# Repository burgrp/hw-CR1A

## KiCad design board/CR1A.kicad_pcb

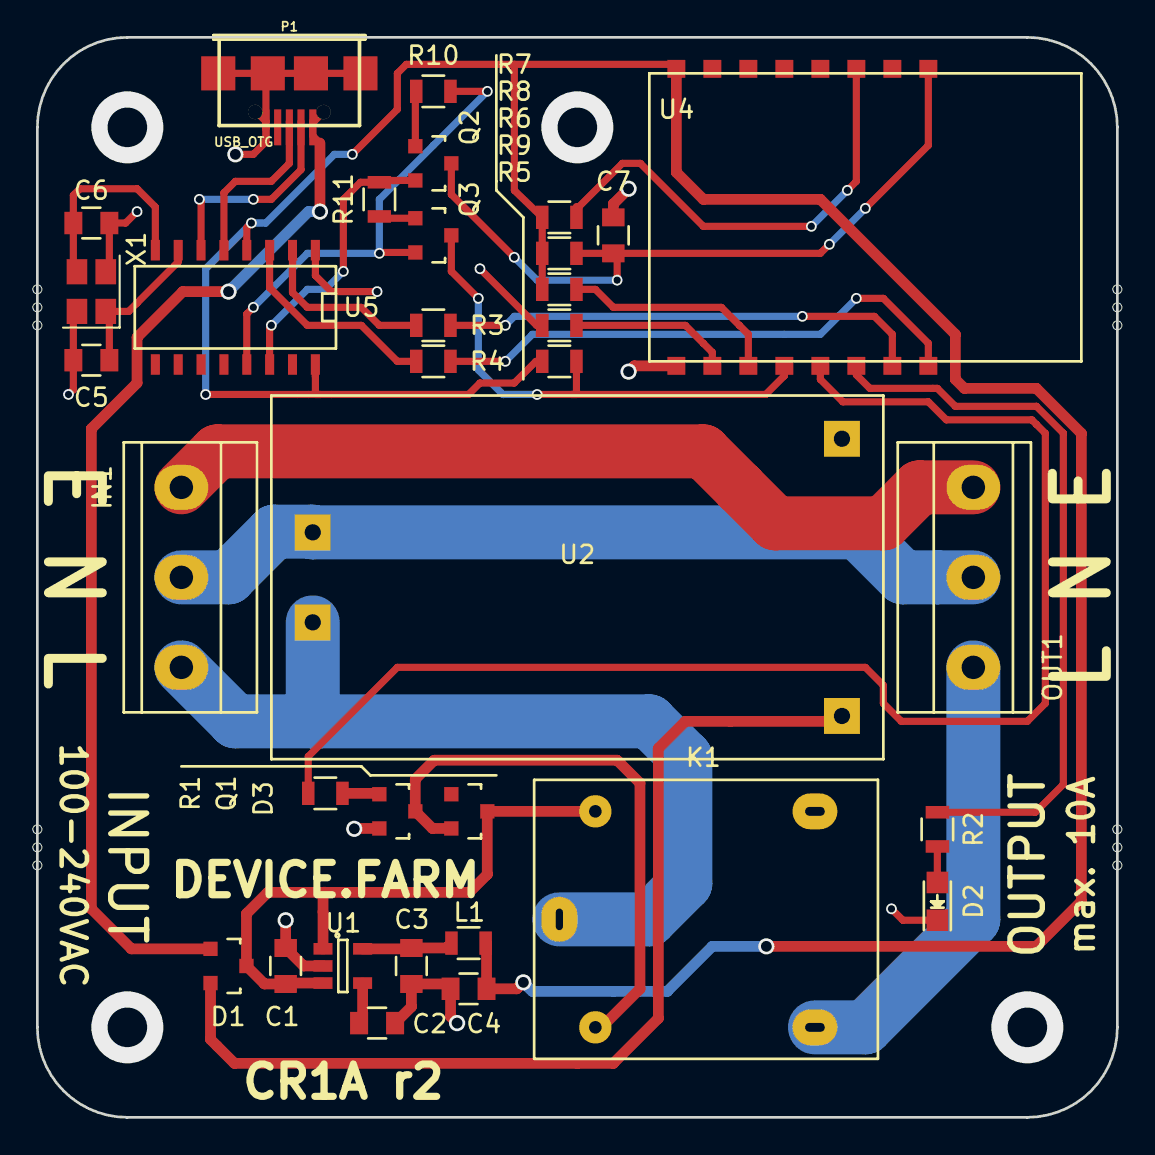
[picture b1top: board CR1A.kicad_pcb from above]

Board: 2 copper layers, 60.0 x 60.0 mm, 38 parts (0 on the bottom side), 33 nets.

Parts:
C1: 1u; C_0805
C2: 22n; C_0805
C3: 47u; C_0805
C4, C7: 100n; C_0805
C5, C6: 22p; C_0805
D1, D3: BAT54C; SOT-23
D2: LED; LED_0805
IN1: CONN_01X03; DG301-5.0-03
K1: RELAY_1; SRD_C_Relay
L1: Ferrite bead; R_0805
MB1, MB2, MB3, MB4: Mill_Bridge; Mill-Bridge
OUT1: CONN_01X03; DG301-5.0-03
P1: USB_OTG; conn_usb_B_micro_smd-2
Q1, Q2, Q3: MMBT3904; SOT-23
R1, R3, R4: 1k5; R_0805
R2: 270R; R_0805
R5, R6, R7, R8, R9, R10, R11: 10k; R_0805
U1: RT9193; SOT-23-5
U2: HLK-PM01
U4: ESP-12
U5: CH340G; SO-16-N
X1: Crystal_GND24; Crystal_SMD_SeikoEpson_TSX3225-4pin_3.2x2.5mm

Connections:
/5V: C1.1, D1.3, D3.3, K1.4, U1.1, U1.3
/ESP/5V-MAINS: D1.2, U2.4
/ESP/5V-USB: D1.1, P1.1
/ESP/D+: P1.3, U5.5
/ESP/D-: P1.2, U5.6
/ESP/DTR: Q3.2, R10.1, U5.13
/ESP/EN: R7.1, U4.3
/ESP/GPIO0: Q3.3, R5.1, U4.12
/ESP/GPIO2: R6.1, U4.11
/ESP/GPIO15: R9.1, U4.10
/ESP/RESET: C7.2, Q2.3, R8.1, U4.1
/ESP/RTS: Q2.2, R11.2, U5.14
/ESP/RX: R3.1, U4.15
/ESP/TX: R4.1, U4.16
/LED: R2.1, U4.14
/MAINS-E: IN1.1, OUT1.3
/MAINS-L-I: IN1.3, K1.5, U2.2
/MAINS-L-O: K1.2, OUT1.1
/MAINS-N: IN1.2, OUT1.2, U2.1
/SW: R1.2, U4.13
GND: C1.2, C2.2, C3.2, C4.2, C5.2, C6.2, C7.1, D2.1, P1.5, P1.6, Q1.2, R9.2, U1.2, U2.3, U4.9, U5.1, X1.2, X1.4
unnamed: C2.1, U1.4
unnamed: C3.1, L1.1, U1.5
unnamed: C5.1, U5.7, X1.1
unnamed: C6.1, U5.8, X1.3
unnamed: D2.2, R2.2
unnamed: D3.2, K1.1, Q1.3
unnamed: Q1.1, R1.1
unnamed: Q2.1, R10.2
unnamed: Q3.1, R11.1
unnamed: R3.2, U5.2
unnamed: R4.2, U5.3
VCC: C4.1, L1.2, R5.2, R6.2, R7.2, R8.2, U4.8, U5.4, U5.16
